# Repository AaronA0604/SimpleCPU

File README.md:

# SimpleCPU
This is a simple CPU that can follow a list of 16 instructions and perform addition, subtraction, and simple logic operations on 2-bit numbers. I made this to learn how to use gates, and it is a good project for people who have experience with hardware but not with gates to try.

It works in several steps. First, the user flips switches in a matrix to manually code the instructions. Then, the user presses run, and those switches tell the ROM, another matrix, what the instructions are. Then, the user powers on the CPU with a switch and resets the counter. Then, the clock starts pulsing 1s and 0s to the counter. The counter then increments by one every clock tick, or jumps a specific amount in certain cases. Next is a decoder that, given the number instructions from the counter, selects a row in the ROM, each of which hold an instruction. The row is inputted into the ALU, which performs the selected operations. Sometimes the instruction will want to use the value from the previous operation, so the accumulator stores the values from the previous operation. Then there is a selector that decides if the ALU gets a new value or the previous output value. The ALU outputs flags, such as negative and zero, which essentially describe the output. The next section then decides whether the program should just go to the next instruction or jump to a different instruction based on those flags. It tells this to the program counter, and the program counter moves to the next part. Then it all repeats.

## Clock

This clock is made of 3 not gates, which invert the value put into them. So, if the input is 1, the output is 0. Because there are an odd number, their output value alternates between 0 and 1 every pass. The 1 is essentially a clock tick. The switch gives power the clock; without it, it can't run. Finally, the and gate is there to only output a value every tick, since it only outputs 1 when the clock value is 1.

## Program Counter (PC)
The job of the PC is to track what step we are on. It moves to the next step or jumps (I'll explain this later) every clock tick.

The first part of the PC is a multiplexer (mux) that takes the number of step we were just on, and a number from the read-only memory that is a step to jump to. It then decides whether it should increment the step we're on by 1 or jump based on an input from the branch logic part of the CPU.

The second part of the PC is an adder. It takes the output from the mux (either 1 for "go to the next step" or another number for a jump) and adds that number to the number of the previous step. It works by using XOR gates, AND gates, and OR gates.

That last part is a register (flip flops that store the value). This keeps track of what number step it is on (a 4 bit number) using 4 slave-master latches (1 for each bit). It also feeds this value back into the adder part of the PC as the value that the increment or jump is added to.

## Read-Only Memory (ROM)
The point of the ROM is to store the instructions to run, and then using the number step from the PC, access the number instruction and send it to the rest of the CPU to run.

The first part of it is a decoder that gets the output from the PC. If that output is 0110 (6), for example, then the decoder makes all of its outputs high except for the 6th output. This means that the CPU is going to run the 6th instruction stored in the ROM.

The ROM stores all of its instructions in this 16x15 matrix. Every row is an instruction, and each column is a different part of that instruction needed to make a full instruction. The matrix is made up of latching switches. They have two coils so that you can turn them on and off electronically (this will make sense when I talk about the assembler), and then they hold their value even while the CPU is off.

This is one latch in the matrix. It is the first one in its row. The row is connected to the NOT gate seen on the left, since as I said earlier the decoder turns all rows high except the one that is chosen, which it turns low. This not gate makes the chosen row high and the others low, which is needed for the CPU to work. It connects to pin 10 on the latch, which is the input pin. The +R and +S coils in this latch are connected to diodes so that their current doesn't leak. The diodes are connected to a row in the assembler (which I'll explain later) so that the latch's value can be changed. Pin 9, the output pin, is connected to a diode so that current doesn't leak to other lines. Then the diode is connected to a wire that runs all the way down the column. Every latch in the same column has a value for the same type. For example, the type could be the 2nd bit of the input value A, or the address that the PC will jump to. At the bottom of every column is a 10k resistor connected to GND.

## Arithmetic Logic Unit (ALU)
The ALU is the heart of the CPU. It does all the computations that are needed for the program. The values for the computation are stored in the ROM, as well as the operation to do to those values. It can only take in 2 values that are each 2 bits.

This part of the ALU is the adder and subtracter. It takes in the 2 2-bit values, denoted as A0, A1, B0, and B1 in this image, and adds or subtracts them based on another input. It works by using XOR gates, AND gates, and OR gates. The AND gate at the top of the image decides whether this adder/subtractor should add or subtract. The AND gate takes two inputs, S0 and S1 (I'll explain where they come from later), and outputs a 1 or 0 to say add or subtract. This output is used as the input for some of the XOR gates. This section of the ALU can both add and subtract, since for subtracting, it inverts the second number, adds it to the first, and adds 1.

This part of the ALU does 4 operations: it can see if values are both 1, see if values are different, see if at least one of the values is 1, or see if none of the values are 1. It uses AND gates, XOR gates, OR gates, and NOT gates respectively to do these different operations.

Since there are many operations that the ALU can do, these two muxes decide which operation to use. The ALU does all of the operations I talked about above the input numbers, but these muxs only let the outputs from one of the operations through. There are 2 muxs, since the inputs are 2 bit numbers and each mux can only deal with one bit. They take in all the outputs from the different operations and also S0, S1, and S2 from the ROM. The S's tell the muxs which value to let through. If those three input values are 010 (2), the muxs let the second value through. I6 on both of them is not being used, so it is tied to GND. They output F0 and F1, which go to the flags, LEDs, and accumulator.

## Flags
Often, the CPU doesn't care what the output number is; it only cares about its characteristics (negative, zero, etc.) These flags describe those characteristics. There are 3 flags: negative, zero, and overflow. Negative sees if the output is negative, zero sees if the output is zero, and overflow sees if the output was more than 2 bits (this could happen if 11 and 11 were added, for example, as that would result in 110).

These gates determine those flags about the output. Note that there are only two gates, for overflow and zero, since the negative flag is simply the output COUT from the adder. The gate for the zero flag is an NAND gate that sees if both F0 and F1 are zero. If they are, it outputs 1, saying that the output from the ALU was 0. The overflow XOR gate takes the COUT output from the adder and the output of the first OR gate in the adder and sees if they are different. If they are, it outputs 1, which means the output from the ALU was more than 2 bits.

## LEDs

These LEDs are a visual output that show both the flag values and the number. From top to bottom, they represent these values: zero flag, negative flag, overflow flag, first digit of output, second digit of output, and third digit of output or a negative sign if the value is being read as signed.

## Accumulator

The accumulator stores the outputs from the ALU in 2 master-slave latches (one for each of the 2 output bits). It takes the output value from the ALU and clock (CLK) as its inputs so it stores the output value and doesn't change it while the clock is in the middle of a tick, since that would mess up its value.

## A Select
Sometimes, we want to do an operation to 2 new values, but sometimes we want to do an operation to an old value, like in a for loop.

Because of this, we have a mux that decides if we want to use a new value for A0 and A1 or the old one. It takes the old value from the accumulator and a new value from the ROM. It also takes a value from the ROM called A_OPCODE, which determines if the output of the mux is the old or new value. Based on that, it outputs 2 bits that are sent to the ALU as the A0 and A1 values.

## Branch Logic
Sometimes, we want to skip to a different instruction based on the output of the last operation.

To decide this, we use a mux and an XOR gate. The mux takes in the flag values and ties all the other unused inputs to GND. It also takes in two bits from the ROM called FLAG0 and FLAG1. These 2 values tell the mux what flag to look at. If those values make the number 01 (1), the mux looks at the first flag. It outputs the value of that flag to the XOR. The XOR then takes another input from the ROM called FLAG_VALUE. FLAG_VALUE says if the program should jump to a different step if the flag value is 0 or 1. Then it outputs JMP to the PC mux, which I mentioned before.

## Set Clock
This is the first piece of the part of the CPU that changes the instructions in the ROM.

The first part of this is the 5-5-5 timer at the top. It and everything attached to it are the actual clock. It's a more complicated version of the clock from before. It outputs SLOW_CLK and its opposite, SLOW_CLK_N.

The AND gate under it takes output from that clock, SLOW_CLK, and also RUN_S, which I'll explain later. If both those values are true, meaning if the clock is pulsing and also RUN_S is on, then it outputs a PULSE.

The NOT gate under that inverts PULSE to PULSE_N.

Under that is a master-slave latch to store two values. It takes the input from a switch, which when it is turned on it means that this reset circuit should run. It also takes SLOW_CLK_N as its second input, and then stores the value of RUN_S and its opposite, RUN_S_N.

The last section is an AND gate that takes RUN_S_N and /RESET (which it gets from the image above) and outputs /RESET_CPU if both those values are on, meaning the set switch is on and the reset button is pressed (which is needed because otherwise the ROM will be messed up).

## Set Counter

This is the counter for the set clock that keeps track of what step it is on. It increases by one every clock pulse. Bar MR is connected to RUN_S so that it only counts if that switch is on. CP is connected to SLOW_CLK_N so that it increases every clock pulse. TC is connected to CEP with an inverter so that it can't count past 16.

This is a decoder, just like the one that connects to the ROM. It takes the value from the counter and makes that output low and every other output high, selecting that row.

## Assembler

This is the final piece in this section, and once you understand it you will understand how this section works. Remember, the point of this section is to write instructions to the ROM. This piece is a matrix that mirrors the ROM, with the same number of rows and columns. It is a bunch of switches that you switch to manually write the instructions. For example if you want the value of A1 in the third step to be one, you go to the third row in the A1 column and flip the switch on, so it is a one. The idea of this matrix is that you manually set all the values, and then you flip the RUN_S switch from before, and it writes all these values to the ROM.

This is one switch in the matrix. It is very simple. It is just connected to a diode so the current doesn't leak, and all you need to do is flip the switch and the value changes.

## Assembler connection to ROM
This is the most complicated part of the CPU. The idea behind it is that the set counter turns on the rows in the assembler one at a time. There is only one row that has power at a time. Then, the values from each of the columns in the assembler pass through gates (I'll explain these later) and a driver to give it enough power to change the values in the ROM. The value from the columns runs down its corresponding column in the ROM, and only changes a latch's value if its row is turned on. This way, by running through every row, every latch can be changed to match the assembler.

These are all the gates for the 15 columns in the ROM.

There are two for every column; one to make the latch value 0, and one to make it 1. The AND gate only lets a one through if the value inputted into it from the column in the assembler is a one, and the NOT gate only lets a one through the value inputted into it from the column in the assembler is a zero. Only one of these gates will output a one at the same time.

These two outputs then go to the driver, which makes their voltage much higher. If its input was a 1 and a 0, it would still output a 1 and a 0, only the 1 would be a higher voltage.

It sends its output to the two coils in the latch. The +S coil is to make the latch a 1, so that pin is only fed from the pin in the driver fed by the AND gate. The +R coil is to make the latch a 0, so that pin is only fed from the pin in the driver fed by the NOT gate.

## PCB

For the PCB, wire it however you'd like. This is a picture of how I wired mine, but you'll have to figure out what works for you.

I recommend adding this chart as the values that you need to set the S0, S1, and S2 columns to in the assembler to do these different operations.

It is also helpful to label your LEDs so you know what they are telling you. Additionally, you can label the columns in the assembler so you know what value each column is. This is what each column is for, from left to right: A0, A1, B0, B1, S0, S1, S2, A_OPCODE, FLAG0, FLAG1, FLAG_VALUE, ADDRESS0, ADDRESS1, ADDRESS2, ADDRESS3.

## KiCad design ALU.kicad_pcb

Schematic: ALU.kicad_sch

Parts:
C1: 10 µF; C_0805_2012Metric
C2: 0.1µF; C_0603_1608Metric
C3: 1µF; C_0603_1608Metric
C4: 10nF; C_0805_2012Metric
D1, D2, D3, D4, D5, D6, D7, D8, D9, D10, D11, D12, D13, D14, D15, D16, D17, D18, D19, D20, D21, D22, D23, D24, D25, D26, D27, D28, D29, D30, D31, D32, D33, D34, D35, D36, D37, D38, D39, D40, D41, D42, D43, D44, D45, D46, D47, D48, D49, D50, D51, D52, D53, D54, D55, D56, D57, D58, D59, D60, D61, D62, D63, D64, D65, D66, D67, D68, D69, D70, D71, D72, D73, D74, D75, D76, D77, D78, D79, D80, D81, D82, D83, D84, D85, D86, D87, D88, D89, D90, D91, D92, D93, D94, D95, D96, D103, D104, D105, D106, D107, D108, D109, D110, D111, D112, D113, D114, D115, D116, D117, D118, D119, D120, D121, D122, D123, D124, D125, D126, D127, D128, D129, D130, D131, D132, D133, D134, D135, D136, D137, D138, D139, D140, D141, D142, D143, D144, D145, D146, D147, D148, D149, D150, D151, D152, D153, D154, D155, D156, D157, D158, D159, D160, D161, D162, D163, D164, D165, D166, D167, D168, D169, D170, D171, D172, D173, D174, D175, D176, D177, D178, D179, D180, D181, D182, D183, D184, D185, D186, D187, D188, D189, D190, D191, D192, D193, D194, D195, D196, D197, D198, D199, D200, D201, D202, D203, D204, D205, D206, D207, D208, D209, D210, D211, D212, D213, D214, D215, D216, D217, D218, D219, D220, D221, D222, D223, D224, D225, D226, D227, D228, D229, D230, D231, D232, D233, D234, D235, D236, D237, D238, D239, D240, D241, D242, D243, D244, D245, D246, D247, D248, D249, D250, D251, D252, D253, D254, D255, D256, D257, D258, D259, D260, D261, D262, D263, D264, D265, D266, D267, D268, D269, D270, D271, D272, D273, D274, D275, D276, D277, D278, D279, D280, D281, D282, D283, D284, D285, D286, D287, D288, D289, D290, D291, D292, D293, D294, D295, D296, D297, D298, D299, D300, D301, D302, D303, D304, D305, D306, D307, D308, D309, D310, D311, D312, D313, D314, D315, D316, D317, D318, D319, D320, D321, D322, D323, D324, D325, D326, D327, D328, D329, D330, D331, D332, D333, D334, D335, D336, D337, D338, D339, D340, D341, D342, D343, D344, D345, D346, D347, D348, D349, D350, D351, D352, D353, D354, D355, D356, D357, D358, D359, D360, D361, D362, D363, D364, D365, D366, D367, D368, D369, D370, D371, D372, D373, D374, D375, D376, D377, D378, D379, D380, D381, D382, D383, D384, D385, D386, D387, D388, D389, D390, D391, D392, D393, D394, D395, D396, D397, D398, D399, D400, D401, D402, D403, D404, D405, D406, D407, D408, D409, D410, D411, D412, D413, D414, D415, D416, D417, D418, D419, D420, D421, D422, D423, D424, D425, D426, D427, D428, D429, D430, D431, D432, D433, D434, D435, D436, D437, D438, D439, D440, D441, D442, D443, D444, D445, D446, D447, D448, D449, D450, D451, D452, D453, D454, D455, D456, D457, D458, D459, D460, D461, D462, D463, D464, D465, D466, D467, D468, D469, D470, D471, D472, D473, D474, D475, D476, D477, D478, D479, D480, D481, D482, D483, D484, D485, D486, D487, D488, D489, D490, D491, D492, D493, D494, D495, D496, D497, D498, D499, D500, D501, D502, D503, D504, D505, D506, D507, D508, D509, D510, D511, D512, D513, D514, D515, D516, D517, D518, D519, D520, D521, D522, D523, D524, D525, D526, D527, D528, D529, D530, D531, D532, D533, D534, D535, D536, D537, D538, D539, D540, D541, D542, D543, D544, D545, D546, D547, D548, D549, D550, D551, D552, D553, D554, D555, D556, D557, D558, D559, D560, D561, D562, D563, D564, D565, D566, D567, D568, D569, D570, D571, D572, D573, D574, D575, D576, D577, D578, D579, D580, D581, D582, D583, D584, D585, D586, D587, D588, D589, D590, D591, D592, D593, D594, D595, D596, D597, D598, D599, D600, D601, D602, D603, D604, D605, D606, D607, D608, D609, D610, D611, D612, D613, D614, D615, D616, D617, D618, D619, D620, D621, D622, D623, D624, D625, D626, D627, D628, D629, D630, D631, D632, D633, D634, D635, D636, D637, D638, D639, D640, D641, D642, D643, D644, D645, D646, D647, D648, D649, D650, D651, D652, D653, D654, D655, D656, D657, D658, D659, D660, D661, D662, D663, D664, D665, D666, D667, D668, D669, D670, D671, D672, D673, D674, D675, D676, D677, D678, D679, D680, D681, D682, D683, D684, D685, D686, D687, D688, D689, D690, D691, D692, D693, D694, D695, D696, D697, D698, D699, D700, D701, D702, D703, D704, D705, D706, D707, D708, D709, D710, D711, D712, D713, D714, D715, D716, D717, D718, D719, D720, D721, D722, D723, D724, D725, D726, D727, D728, D729, D730, D731, D732, D733, D734, D735, D736, D737, D738, D739, D740, D741, D742, D743, D744, D745, D746, D747, D748, D749, D750, D751, D752, D753, D754, D755, D756, D757, D758, D759, D760, D761, D762, D763, D764, D765, D766, D767, D768, D769, D770, D771, D772, D773, D774, D775, D776, D777, D778, D779, D780, D781, D782, D783, D784, D785, D786, D787, D788, D789, D790, D791, D792, D793, D794, D795, D796, D797, D798, D799, D800, D801, D802, D803, D804, D805, D806, D807, D808, D809, D810, D811, D812, D813, D814, D815, D816, D817, D818, D819, D820, D821, D822, D823, D824, D825, D826, D827, D828, D829, D830, D831, D832, D833, D834, D835, D836, D837, D838, D839, D840, D841, D842, D843, D844, D845, D846, D847, D848, D849, D850, D851, D852, D853, D854, D855, D856, D857, D858, D859, D860, D861, D862, D863, D864, D865, D866, D867, D868, D869, D870, D871, D872, D873, D874, D875, D876, D877, D878, D879, D880, D881, D882, D883, D884, D885, D886, D887, D888, D889, D890, D891, D892, D893, D894, D895, D896, D897, D898, D899, D900, D901, D902, D903, D904, D905, D906, D907, D908, D909, D910, D911, D912, D913, D914, D915, D916, D917, D918, D919, D920, D921, D922, D923, D924, D925, D926, D927, D928, D929, D930, D931, D932, D933, D934, D935, D936, D937, D938, D939, D940, D941, D942, D943, D944, D945, D946, D947, D948, D949, D950, D951, D952, D953, D954, D955, D956, D957, D958, D959, D960, D961, D962, D963, D964, D965, D966: D; D_DO-35_SOD27_P7.62mm_Horizontal
D97, D98, D99, D100, D101, D102: LED; LED_D5.0mm
K1, K2, K3, K4, K5, K6, K7, K8, K9, K10, K11, K12, K13, K14, K15, K16, K17, K18, K19, K20, K21, K22, K23, K24, K25, K26, K27, K28, K29, K30, K31, K32, K33, K34, K35, K36, K37, K38, K39, K40, K41, K42, K43, K44, K45, K46, K47, K48, K49, K50, K51, K52, K53, K54, K55, K56, K57, K58, K59, K60, K61, K62, K63, K64, K65, K66, K67, K68, K69, K70, K71, K72, K73, K74, K75, K76, K77, K78, K79, K80, K81, K82, K83, K84, K85, K86, K87, K88, K89, K90, K91, K92, K93, K94, K95, K96, K97, K98, K99, K100, K101, K102, K103, K104, K105, K106, K107, K108, K109, K110, K111, K112, K113, K114, K115, K116, K117, K118, K119, K120, K121, K122, K123, K124, K125, K126, K127, K128, K129, K130, K131, K132, K133, K134, K135, K136, K137, K138, K139, K140, K141, K142, K143, K144, K145, K146, K147, K148, K149, K150, K151, K152, K153, K154, K155, K156, K157, K158, K159, K160, K161, K162, K163, K164, K165, K166, K167, K168, K169, K170, K171, K172, K173, K174, K175, K176, K177, K178, K179, K180, K181, K182, K183, K184, K185, K186, K187, K188, K189, K190, K191, K192, K193, K194, K195, K196, K197, K198, K199, K200, K201, K202, K203, K204, K205, K206, K207, K208, K209, K210, K211, K212, K213, K214, K215, K216, K217, K218, K219, K220, K221, K222, K223, K224, K225, K226, K227, K228, K229, K230, K231, K232, K233, K234, K235, K236, K237, K238, K239, K240: EC2-5TNU; Relay_DPDT_Kemet_EC2_NU_DoubleCoil
Q1, Q2, Q3, Q4, Q5, Q6, Q7, Q8, Q9, Q10, Q11, Q12, Q13, Q14, Q15, Q16: BC327; TO-92_Inline
R1, R2, R9, R10, R11, R12, R13, R14, R15, R16, R17, R18, R19, R20, R21, R22, R23, R41, R42, R43, R44, R45, R46, R47, R48, R49, R50, R51, R52, R53, R54, R55: 10k; R_Axial_DIN0207_L6.3mm_D2.5mm_P10.16mm_Horizontal
R3, R4, R5, R6, R7, R8: 330 Ω; R_Axial_DIN0207_L6.3mm_D2.5mm_P10.16mm_Horizontal
R24, R25, R26, R27, R28, R29, R30, R31, R32, R33, R34, R35, R36, R37, R38, R39, R40: 1k; R_Axial_DIN0207_L6.3mm_D2.5mm_P10.16mm_Horizontal
RV1: 100k; Pololu_Breakout-16_15.2x20.3mm
SW1: SW_Push; SW_PUSH_6mm
SW2, SW3, SW4, SW5, SW6, SW7, SW8, SW9, SW10, SW11, SW12, SW13, SW14, SW15, SW16, SW17, SW18, SW19, SW20, SW21, SW22, SW23, SW24, SW25, SW26, SW27, SW28, SW29, SW30, SW31, SW32, SW33, SW34, SW35, SW36, SW37, SW38, SW39, SW40, SW41, SW42, SW43, SW44, SW45, SW46, SW47, SW48, SW49, SW50, SW51, SW52, SW53, SW54, SW55, SW56, SW57, SW58, SW59, SW60, SW61, SW62, SW63, SW64, SW65, SW66, SW67, SW68, SW69, SW70, SW71, SW72, SW73, SW74, SW75, SW76, SW77, SW78, SW79, SW80, SW81, SW82, SW83, SW84, SW85, SW86, SW87, SW88, SW89, SW90, SW91, SW92, SW93, SW94, SW95, SW96, SW97, SW98, SW99, SW100, SW101, SW102, SW103, SW104, SW105, SW106, SW107, SW108, SW109, SW110, SW111, SW112, SW113, SW114, SW115, SW116, SW117, SW118, SW119, SW120, SW121, SW122, SW123, SW124, SW125, SW126, SW127, SW128, SW129, SW130, SW131, SW132, SW133, SW134, SW135, SW136, SW137, SW138, SW139, SW140, SW141, SW142, SW143, SW144, SW145, SW146, SW147, SW148, SW149, SW150, SW151, SW152, SW153, SW154, SW155, SW156, SW157, SW158, SW159, SW160, SW161, SW162, SW163, SW164, SW165, SW166, SW167, SW168, SW169, SW170, SW171, SW172, SW173, SW174, SW175, SW176, SW177, SW178, SW179, SW180, SW181, SW182, SW183, SW184, SW185, SW186, SW187, SW188, SW189, SW190, SW191, SW192, SW193, SW194, SW195, SW196, SW197, SW198, SW199, SW200, SW201, SW202, SW203, SW204, SW205, SW206, SW207, SW208, SW209, SW210, SW211, SW212, SW213, SW214, SW215, SW216, SW217, SW218, SW219, SW220, SW221, SW222, SW223, SW224, SW225, SW226, SW227, SW228, SW229, SW230, SW231, SW232, SW233, SW234, SW235, SW236, SW237, SW238, SW239, SW240, SW241, SW242, SW243: SW_SPDT; Nidec_Copal_CAS-120A
U1, U5, U10, U20, U21: 74HC86; DIP-14_W7.62mm
U2, U4, U19, U22, U34, U36, U38, U40, U44, U47, U50: 7408; DIP-14_W7.62mm
U3, U6, U23: 7432; DIP-14_W7.62mm
U7, U16, U27, U28, U29, U45: 74HC04; DIP-14_W7.62mm
U8, U9: 74LS151; DIP-16_W7.62mm
U11, U35, U37, U39, U41: 74HCT02; DIP-14_W7.62mm
U12, U24, U25, U46: 74HC74; DIP-14_W7.62mm
U13: 74LS157; DIP-16_W7.62mm
U14: 74LS153; DIP-16_W7.62mm
U15: 4077; DIP-14_W7.62mm
U17, U43: 74HC14; DIP-14_W7.62mm
U18: 74LS157; DIP-14_W7.62mm
U26, U49: 74LS154; DIP-24_W15.24mm
U30, U31, U32, U33: ULN2803A; DIP-18_W7.62mm
U42: ICM7555xB; SOIC-8_3.9x4.9mm_P1.27mm
U48: 74LS161; DIP-16_W7.62mm

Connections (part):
+5V: C2.1, Q1.1 (C), Q2.1 (C), Q3.1 (C), Q4.1 (C), Q5.1 (C), Q6.1 (C), Q7.1 (C), Q8.1 (C), Q9.1 (C), Q10.1 (C), Q11.1 (C), Q12.1 (C), Q13.1 (C), Q14.1 (C), Q15.1 (C), Q16.1 (C), R1.2, R24.1, R41.1, R42.1, R43.1, R44.1, R45.1, R46.1, R47.1, R48.1, R49.1, R50.1, R51.1, R52.1, R53.1, R54.1, R55.1, SW2.1 (A), SW3.3 (C), U1.14 (VCC), U2.14 (VCC), U3.14 (VCC), U4.14 (VCC), U5.14 (VCC), U6.14 (VCC), U8.16 (VCC), U9.16 (VCC), U10.14 (VCC), U11.14 (VCC), U12.1 (~R), U12.4 (~S), U12.10 (~S), U12.13 (~R), U12.14 (VCC), U13.16 (VCC), U14.16 (VCC), U15.14 (VDD), U16.14 (VCC), U17.14 (VCC), U18.16 (VCC), U19.14 (VCC), U20.14 (VCC), U21.14 (VCC), U22.14 (VCC), U23.14 (VCC), U24.4 (~S), U24.10 (~S), U24.14 (VCC), U25.4 (~S), U25.10 (~S), U25.14 (VCC), U26.24 (VCC), U27.14 (VCC), U28.14 (VCC), U29.14 (VCC), U30.10 (COM), U31.10 (COM), U32.10 (COM), U33.10 (COM), U34.14 (VCC), U35.14 (VCC), U36.14 (VCC), U37.14 (VCC)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
/A0: D33.1 (K), D34.1 (K), D35.1 (K), D36.1 (K), D37.1 (K), D38.1 (K), D39.1 (K), D40.1 (K), D41.1 (K), D42.1 (K), D43.1 (K), D44.1 (K), D45.1 (K), D46.1 (K), D47.1 (K), D48.1 (K), R2.1, U13.3 (I1a)
/A0_SELECTED: U1.9, U2.1, U4.1, U5.1, U6.1, U7.1, U9.13 (I6), U13.4 (Za)
/A1: D81.1 (K), D82.1 (K), D83.1 (K), D84.1 (K), D85.1 (K), D86.1 (K), D87.1 (K), D88.1 (K), D89.1 (K), D90.1 (K), D91.1 (K), D92.1 (K), D93.1 (K), D94.1 (K), D95.1 (K), D96.1 (K), R9.1, U13.6 (I1b)
/A1_SELECTED: U1.12, U2.4, U4.4, U5.4, U6.4, U13.7 (Zb)
/ACCUMULATOR0: U12.5 (Q), U13.2 (I0a)
/ACCUMULATOR1: U12.9 (Q), U13.5 (I0b)
/ADDRESS0: D565.1 (K), D566.1 (K), D567.1 (K), D568.1 (K), D569.1 (K), D570.1 (K), D571.1 (K), D572.1 (K), D573.1 (K), D574.1 (K), D575.1 (K), D576.1 (K), D577.1 (K), D578.1 (K), D579.1 (K), D580.1 (K), R19.1, U18.3 (I1a)
/ADDRESS1: D613.1 (K), D614.1 (K), D615.1 (K), D616.1 (K), D617.1 (K), D618.1 (K), D619.1 (K), D620.1 (K), D621.1 (K), D622.1 (K), D623.1 (K), D624.1 (K), D625.1 (K), D626.1 (K), D627.1 (K), D628.1 (K), R20.1, U18.6 (I1b)
/ADDRESS2: D661.1 (K), D662.1 (K), D663.1 (K), D664.1 (K), D665.1 (K), D666.1 (K), D667.1 (K), D668.1 (K), D669.1 (K), D670.1 (K), D671.1 (K), D672.1 (K), D673.1 (K), D674.1 (K), D675.1 (K), D676.1 (K), R21.1, U18.10 (I1c)
/ADDRESS3: D709.1 (K), D710.1 (K), D711.1 (K), D712.1 (K), D713.1 (K), D714.1 (K), D715.1 (K), D716.1 (K), D717.1 (K), D718.1 (K), D719.1 (K), D720.1 (K), D721.1 (K), D722.1 (K), D723.1 (K), D724.1 (K), R22.1, U18.13 (I1d)
/AND0: U4.3, U8.4 (I0)
/AND1: U4.6, U9.4 (I0)
/A_OPCODE: D373.1 (K), D374.1 (K), D375.1 (K), D376.1 (K), D377.1 (K), D378.1 (K), D379.1 (K), D380.1 (K), D381.1 (K), D382.1 (K), D383.1 (K), D384.1 (K), D385.1 (K), D386.1 (K), D387.1 (K), D388.1 (K), R15.1, U13.1 (S)
/B0: D135.1 (K), D136.1 (K), D137.1 (K), D138.1 (K), D139.1 (K), D140.1 (K), D141.1 (K), D142.1 (K), D143.1 (K), D144.1 (K), D145.1 (K), D146.1 (K), D147.1 (K), D148.1 (K), D149.1 (K), D150.1 (K), R10.1, U1.2, U4.2, U5.2, U6.2, U7.3, U8.12 (I7)
/B1: D183.1 (K), D184.1 (K), D185.1 (K), D186.1 (K), D187.1 (K), D188.1 (K), D189.1 (K), D190.1 (K), D191.1 (K), D192.1 (K), D193.1 (K), D194.1 (K), D195.1 (K), D196.1 (K), D197.1 (K), D198.1 (K), R11.1, U1.5, U4.5, U5.5, U6.5
/C0: D725.2 (A), D726.2 (A), D727.2 (A), D728.2 (A), D729.2 (A), D730.2 (A), D731.2 (A), D732.2 (A), D733.2 (A), D734.2 (A), D735.2 (A), D736.2 (A), D737.2 (A), D738.2 (A), D739.2 (A), D740.2 (A), R41.2, U34.2, U35.3
/C1: D741.2 (A), D742.2 (A), D743.2 (A), D744.2 (A), D745.2 (A), D746.2 (A), D747.2 (A), D748.2 (A), D749.2 (A), D750.2 (A), D751.2 (A), D752.2 (A), D753.2 (A), D754.2 (A), D755.2 (A), D756.2 (A), R42.2, U34.5, U35.6
/C2: D757.2 (A), D758.2 (A), D759.2 (A), D760.2 (A), D761.2 (A), D762.2 (A), D763.2 (A), D764.2 (A), D765.2 (A), D766.2 (A), D767.2 (A), D768.2 (A), D769.2 (A), D770.2 (A), D771.2 (A), D772.2 (A), R43.2, U34.10, U35.9
/C3: D773.2 (A), D774.2 (A), D775.2 (A), D776.2 (A), D777.2 (A), D778.2 (A), D779.2 (A), D780.2 (A), D781.2 (A), D782.2 (A), D783.2 (A), D784.2 (A), D785.2 (A), D786.2 (A), D787.2 (A), D788.2 (A), R44.2, U34.13, U35.12
/C4: D789.2 (A), D790.2 (A), D791.2 (A), D792.2 (A), D793.2 (A), D794.2 (A), D795.2 (A), D796.2 (A), D797.2 (A), D798.2 (A), D799.2 (A), D800.2 (A), D801.2 (A), D802.2 (A), D803.2 (A), D804.2 (A), R45.2, U36.2, U37.3
/C5: D805.2 (A), D806.2 (A), D807.2 (A), D808.2 (A), D809.2 (A), D810.2 (A), D811.2 (A), D812.2 (A), D813.2 (A), D814.2 (A), D815.2 (A), D816.2 (A), D817.2 (A), D818.2 (A), D819.2 (A), D820.2 (A), R46.2, U36.5, U37.6
/C6: D821.2 (A), D822.2 (A), D823.2 (A), D824.2 (A), D825.2 (A), D826.2 (A), D827.2 (A), D828.2 (A), D829.2 (A), D830.2 (A), D831.2 (A), D832.2 (A), D833.2 (A), D834.2 (A), D835.2 (A), D836.2 (A), R47.2, U36.10, U37.9
/C7: D837.2 (A), D838.2 (A), D839.2 (A), D840.2 (A), D841.2 (A), D842.2 (A), D843.2 (A), D844.2 (A), D845.2 (A), D846.2 (A), D847.2 (A), D848.2 (A), D849.2 (A), D850.2 (A), D851.2 (A), D852.2 (A), R48.2, U36.13, U37.12
/C8: D853.2 (A), D854.2 (A), D855.2 (A), D856.2 (A), D857.2 (A), D858.2 (A), D859.2 (A), D860.2 (A), D861.2 (A), D862.2 (A), D863.2 (A), D864.2 (A), D865.2 (A), D866.2 (A), D867.2 (A), D868.2 (A), R49.2, U38.2, U39.3
/C9: D869.2 (A), D870.2 (A), D871.2 (A), D872.2 (A), D873.2 (A), D874.2 (A), D875.2 (A), D876.2 (A), D877.2 (A), D878.2 (A), D879.2 (A), D880.2 (A), D881.2 (A), D882.2 (A), D883.2 (A), D884.2 (A), R50.2, U38.5, U39.6
/C10: D885.2 (A), D886.2 (A), D887.2 (A), D888.2 (A), D889.2 (A), D890.2 (A), D891.2 (A), D892.2 (A), D893.2 (A), D894.2 (A), D895.2 (A), D896.2 (A), D897.2 (A), D898.2 (A), D899.2 (A), D900.2 (A), R51.2, U38.10, U39.9
/C11: D901.2 (A), D902.2 (A), D903.2 (A), D904.2 (A), D905.2 (A), D906.2 (A), D907.2 (A), D908.2 (A), D909.2 (A), D910.2 (A), D911.2 (A), D912.2 (A), D913.2 (A), D914.2 (A), D915.2 (A), D916.2 (A), R52.2, U38.13, U39.12
/C12: D917.2 (A), D918.2 (A), D919.2 (A), D920.2 (A), D921.2 (A), D922.2 (A), D923.2 (A), D924.2 (A), D925.2 (A), D926.2 (A), D927.2 (A), D928.2 (A), D929.2 (A), D930.2 (A), D931.2 (A), D932.2 (A), R53.2, U40.2, U41.3
/C13: D933.2 (A), D934.2 (A), D935.2 (A), D936.2 (A), D937.2 (A), D938.2 (A), D939.2 (A), D940.2 (A), D941.2 (A), D942.2 (A), D943.2 (A), D944.2 (A), D945.2 (A), D946.2 (A), D947.2 (A), D948.2 (A), R54.2, U40.5, U41.6
/C14: D949.2 (A), D950.2 (A), D951.2 (A), D952.2 (A), D953.2 (A), D954.2 (A), D955.2 (A), D956.2 (A), D957.2 (A), D958.2 (A), D959.2 (A), D960.2 (A), D961.2 (A), D962.2 (A), D963.2 (A), D964.2 (A), R55.2, U40.10, U41.9
/CLK: U12.3 (C), U12.11 (C), U18.2 (I0a), U19.3, U24.3 (C), U24.11 (C), U25.3 (C), U25.11 (C)
/COUT: R8.1, U3.6, U10.9
/F0: R6.1, U8.5 (Z), U11.2, U12.2 (D)
/F1: R4.1, R7.1, U9.5 (Z), U11.3, U12.12 (D), U14.5 (I1a)
/FLAG0: D421.1 (K), D422.1 (K), D423.1 (K), D424.1 (K), D425.1 (K), D426.1 (K), D427.1 (K), D428.1 (K), D429.1 (K), D430.1 (K), D431.1 (K), D432.1 (K), D433.1 (K), D434.1 (K), D435.1 (K), D436.1 (K), R16.1, U14.14 (S0)
/FLAG1: D469.1 (K), D470.1 (K), D471.1 (K), D472.1 (K), D473.1 (K), D474.1 (K), D475.1 (K), D476.1 (K), D477.1 (K), D478.1 (K), D479.1 (K), D480.1 (K), D481.1 (K), D482.1 (K), D483.1 (K), D484.1 (K), R17.1, U14.2 (S1)
/FLAG_VALUE: D517.1 (K), D518.1 (K), D519.1 (K), D520.1 (K), D521.1 (K), D522.1 (K), D523.1 (K), D524.1 (K), D525.1 (K), D526.1 (K), D527.1 (K), D528.1 (K), D529.1 (K), D530.1 (K), D531.1 (K), D532.1 (K), R18.1, U15.2
/JMP: U15.3, U18.1 (S)
/NOT0: U7.2, U8.14 (I5)
/NOT1: U7.4, U9.14 (I5)
/OR0: U6.3, U8.15 (I4)
/OR1: U6.6, U9.15 (I4)
/OVERFLOW: R5.1, U10.8, U14.4 (I2a)
/PC0: U19.4, U20.1, U24.5 (Q), U26.23 (A0)
/PC1: U19.9, U20.4, U24.9 (Q), U26.22 (A1)
/PC2: U19.12, U20.9, U25.5 (Q), U26.21 (A2)
/PC3: U20.12, U25.9 (Q), U26.20 (A3)
/PC_VALUE0: U20.3, U24.2 (D)
/PC_VALUE1: U21.3, U24.12 (D)
/PC_VALUE2: U21.6, U25.2 (D)
/PC_VALUE3: U21.8, U25.12 (D)
/PULSE: U34.1, U34.4, U34.9, U34.12, U36.1, U36.4, U36.9, U36.12, U38.1, U38.4, U38.9, U38.12, U40.1, U40.4, U40.9, U44.3, U45.1
/PULSE_N: U35.2, U35.5, U35.8, U35.11, U37.2, U37.5, U37.8, U37.11, U39.2, U39.5, U39.8, U39.11, U41.2, U41.5, U41.8, U45.2
/P_ROW0: D1.2 (A), D2.2 (A), D49.2 (A), D50.2 (A), D103.2 (A), D104.2 (A), D151.2 (A), D152.2 (A), D199.2 (A), D200.2 (A), D247.2 (A), D248.2 (A), D293.2 (A), D294.2 (A), D341.2 (A), D342.2 (A), D389.2 (A), D390.2 (A), D437.2 (A), D438.2 (A), D485.2 (A), D486.2 (A), D533.2 (A), D534.2 (A), D581.2 (A), D582.2 (A), D629.2 (A), D630.2 (A), D677.2 (A), D678.2 (A), Q1.3 (E), SW4.1 (A), SW20.1 (A), SW36.1 (A), SW52.1 (A), SW68.1 (A), SW84.1 (A), SW100.1 (A), SW116.1 (A), SW132.1 (A), SW148.1 (A), SW164.1 (A), SW180.1 (A), SW196.1 (A), SW212.1 (A), SW228.1 (A)
/P_ROW1: D3.2 (A), D4.2 (A), D51.2 (A), D52.2 (A), D105.2 (A), D106.2 (A), D153.2 (A), D154.2 (A), D201.2 (A), D202.2 (A), D249.2 (A), D250.2 (A), D295.2 (A), D296.2 (A), D343.2 (A), D344.2 (A), D391.2 (A), D392.2 (A), D439.2 (A), D440.2 (A), D487.2 (A), D488.2 (A), D535.2 (A), D536.2 (A), D583.2 (A), D584.2 (A), D631.2 (A), D632.2 (A), D679.2 (A), D680.2 (A), Q2.3 (E), SW5.1 (A), SW21.1 (A), SW37.1 (A), SW53.1 (A), SW69.1 (A), SW85.1 (A), SW101.1 (A), SW117.1 (A), SW133.1 (A), SW149.1 (A), SW165.1 (A), SW181.1 (A), SW197.1 (A), SW213.1 (A), SW229.1 (A)
/P_ROW2: D5.2 (A), D6.2 (A), D53.2 (A), D54.2 (A), D107.2 (A), D108.2 (A), D155.2 (A), D156.2 (A), D203.2 (A), D204.2 (A), D251.2 (A), D252.2 (A), D297.2 (A), D298.2 (A), D345.2 (A), D346.2 (A), D393.2 (A), D394.2 (A), D441.2 (A), D442.2 (A), D489.2 (A), D490.2 (A), D537.2 (A), D538.2 (A), D585.2 (A), D586.2 (A), D633.2 (A), D634.2 (A), D681.2 (A), D682.2 (A), Q3.3 (E), SW6.1 (A), SW22.1 (A), SW38.1 (A), SW54.1 (A), SW70.1 (A), SW86.1 (A), SW102.1 (A), SW118.1 (A), SW134.1 (A), SW150.1 (A), SW166.1 (A), SW182.1 (A), SW198.1 (A), SW214.1 (A), SW230.1 (A)
/P_ROW3: D7.2 (A), D8.2 (A), D55.2 (A), D56.2 (A), D109.2 (A), D110.2 (A), D157.2 (A), D158.2 (A), D205.2 (A), D206.2 (A), D299.2 (A), D300.2 (A), D347.2 (A), D348.2 (A), D395.2 (A), D396.2 (A), D443.2 (A), D444.2 (A), D491.2 (A), D492.2 (A), D539.2 (A), D540.2 (A), D587.2 (A), D588.2 (A), D635.2 (A), D636.2 (A), D683.2 (A), D684.2 (A), D965.2 (A), D966.2 (A), Q4.3 (E), SW7.1 (A), SW23.1 (A), SW39.1 (A), SW55.1 (A), SW71.1 (A), SW87.1 (A), SW103.1 (A), SW119.1 (A), SW135.1 (A), SW151.1 (A), SW167.1 (A), SW183.1 (A), SW199.1 (A), SW215.1 (A), SW231.1 (A)
/P_ROW4: D9.2 (A), D10.2 (A), D57.2 (A), D58.2 (A), D111.2 (A), D112.2 (A), D159.2 (A), D160.2 (A), D207.2 (A), D208.2 (A), D253.2 (A), D254.2 (A), D301.2 (A), D302.2 (A), D349.2 (A), D350.2 (A), D397.2 (A), D398.2 (A), D445.2 (A), D446.2 (A), D493.2 (A), D494.2 (A), D541.2 (A), D542.2 (A), D589.2 (A), D590.2 (A), D637.2 (A), D638.2 (A), D685.2 (A), D686.2 (A), Q5.3 (E), SW8.1 (A), SW24.1 (A), SW40.1 (A), SW56.1 (A), SW72.1 (A), SW88.1 (A), SW104.1 (A), SW120.1 (A), SW136.1 (A), SW152.1 (A), SW168.1 (A), SW184.1 (A), SW200.1 (A), SW216.1 (A), SW232.1 (A)
/P_ROW5: D11.2 (A), D12.2 (A), D59.2 (A), D60.2 (A), D113.2 (A), D114.2 (A), D161.2 (A), D162.2 (A), D209.2 (A), D210.2 (A), D255.2 (A), D256.2 (A), D303.2 (A), D304.2 (A), D351.2 (A), D352.2 (A), D399.2 (A), D400.2 (A), D447.2 (A), D448.2 (A), D495.2 (A), D496.2 (A), D543.2 (A), D544.2 (A), D591.2 (A), D592.2 (A), D639.2 (A), D640.2 (A), D687.2 (A), D688.2 (A), Q6.3 (E), SW9.1 (A), SW25.1 (A), SW41.1 (A), SW57.1 (A), SW73.1 (A), SW89.1 (A), SW105.1 (A), SW121.1 (A), SW137.1 (A), SW153.1 (A), SW169.1 (A), SW185.1 (A), SW201.1 (A), SW217.1 (A), SW233.1 (A)
/P_ROW6: D13.2 (A), D14.2 (A), D61.2 (A), D62.2 (A), D115.2 (A), D116.2 (A), D163.2 (A), D164.2 (A), D211.2 (A), D212.2 (A), D257.2 (A), D258.2 (A), D305.2 (A), D306.2 (A), D353.2 (A), D354.2 (A), D401.2 (A), D402.2 (A), D449.2 (A), D450.2 (A), D497.2 (A), D498.2 (A), D545.2 (A), D546.2 (A), D593.2 (A), D594.2 (A), D641.2 (A), D642.2 (A), D689.2 (A), D690.2 (A), Q7.3 (E), SW10.1 (A), SW26.1 (A), SW42.1 (A), SW58.1 (A), SW74.1 (A), SW90.1 (A), SW106.1 (A), SW122.1 (A), SW138.1 (A), SW154.1 (A), SW170.1 (A), SW186.1 (A), SW202.1 (A), SW218.1 (A), SW234.1 (A)
/P_ROW7: D15.2 (A), D16.2 (A), D63.2 (A), D64.2 (A), D117.2 (A), D118.2 (A), D165.2 (A), D166.2 (A), D213.2 (A), D214.2 (A), D259.2 (A), D260.2 (A), D307.2 (A), D308.2 (A), D355.2 (A), D356.2 (A), D403.2 (A), D404.2 (A), D451.2 (A), D452.2 (A), D499.2 (A), D500.2 (A), D547.2 (A), D548.2 (A), D595.2 (A), D596.2 (A), D643.2 (A), D644.2 (A), D691.2 (A), D692.2 (A), Q8.3 (E), SW11.1 (A), SW27.1 (A), SW43.1 (A), SW59.1 (A), SW75.1 (A), SW91.1 (A), SW107.1 (A), SW123.1 (A), SW139.1 (A), SW155.1 (A), SW171.1 (A), SW187.1 (A), SW203.1 (A), SW219.1 (A), SW235.1 (A)
/P_ROW8: D17.2 (A), D18.2 (A), D65.2 (A), D66.2 (A), D119.2 (A), D120.2 (A), D167.2 (A), D168.2 (A), D215.2 (A), D216.2 (A), D261.2 (A), D262.2 (A), D309.2 (A), D310.2 (A), D357.2 (A), D358.2 (A), D405.2 (A), D406.2 (A), D453.2 (A), D454.2 (A), D501.2 (A), D502.2 (A), D549.2 (A), D550.2 (A), D597.2 (A), D598.2 (A), D645.2 (A), D646.2 (A), D693.2 (A), D694.2 (A), Q9.3 (E), SW12.1 (A), SW28.1 (A), SW44.1 (A), SW60.1 (A), SW76.1 (A), SW92.1 (A), SW108.1 (A), SW124.1 (A), SW140.1 (A), SW156.1 (A), SW172.1 (A), SW188.1 (A), SW204.1 (A), SW220.1 (A), SW236.1 (A)
/P_ROW9: D19.2 (A), D20.2 (A), D67.2 (A), D68.2 (A), D121.2 (A), D122.2 (A), D169.2 (A), D170.2 (A), D217.2 (A), D218.2 (A), D263.2 (A), D264.2 (A), D311.2 (A), D312.2 (A), D359.2 (A), D360.2 (A), D407.2 (A), D408.2 (A), D455.2 (A), D456.2 (A), D503.2 (A), D504.2 (A), D551.2 (A), D552.2 (A), D599.2 (A), D600.2 (A), D647.2 (A), D648.2 (A), D695.2 (A), D696.2 (A), Q10.3 (E), SW13.1 (A), SW29.1 (A), SW45.1 (A), SW61.1 (A), SW77.1 (A), SW93.1 (A), SW109.1 (A), SW125.1 (A), SW141.1 (A), SW157.1 (A), SW173.1 (A), SW189.1 (A), SW205.1 (A), SW221.1 (A), SW237.1 (A)
/P_ROW10: D21.2 (A), D22.2 (A), D69.2 (A), D70.2 (A), D123.2 (A), D124.2 (A), D171.2 (A), D172.2 (A), D219.2 (A), D220.2 (A), D265.2 (A), D266.2 (A), D313.2 (A), D314.2 (A), D361.2 (A), D362.2 (A), D409.2 (A), D410.2 (A), D457.2 (A), D458.2 (A), D505.2 (A), D506.2 (A), D553.2 (A), D554.2 (A), D601.2 (A), D602.2 (A), D649.2 (A), D650.2 (A), D697.2 (A), D698.2 (A), Q11.3 (E), SW14.1 (A), SW30.1 (A), SW46.1 (A), SW62.1 (A), SW78.1 (A), SW94.1 (A), SW110.1 (A), SW126.1 (A), SW142.1 (A), SW158.1 (A), SW174.1 (A), SW190.1 (A), SW206.1 (A), SW222.1 (A), SW238.1 (A)
/P_ROW11: D23.2 (A), D24.2 (A), D71.2 (A), D72.2 (A), D125.2 (A), D126.2 (A), D173.2 (A), D174.2 (A), D221.2 (A), D222.2 (A), D267.2 (A), D268.2 (A), D315.2 (A), D316.2 (A), D363.2 (A), D364.2 (A), D411.2 (A), D412.2 (A), D459.2 (A), D460.2 (A), D507.2 (A), D508.2 (A), D555.2 (A), D556.2 (A), D603.2 (A), D604.2 (A), D651.2 (A), D652.2 (A), D699.2 (A), D700.2 (A), Q12.3 (E), SW15.1 (A), SW31.1 (A), SW47.1 (A), SW63.1 (A), SW79.1 (A), SW95.1 (A), SW111.1 (A), SW127.1 (A), SW143.1 (A), SW159.1 (A), SW175.1 (A), SW191.1 (A), SW207.1 (A), SW223.1 (A), SW239.1 (A)
/P_ROW12: D25.2 (A), D26.2 (A), D73.2 (A), D74.2 (A), D127.2 (A), D128.2 (A), D175.2 (A), D176.2 (A), D223.2 (A), D224.2 (A), D269.2 (A), D270.2 (A), D317.2 (A), D318.2 (A), D365.2 (A), D366.2 (A), D413.2 (A), D414.2 (A), D461.2 (A), D462.2 (A), D509.2 (A), D510.2 (A), D557.2 (A), D558.2 (A), D605.2 (A), D606.2 (A), D653.2 (A), D654.2 (A), D701.2 (A), D702.2 (A), Q13.3 (E), SW16.1 (A), SW32.1 (A), SW48.1 (A), SW64.1 (A), SW80.1 (A), SW96.1 (A), SW112.1 (A), SW128.1 (A), SW144.1 (A), SW160.1 (A), SW176.1 (A), SW192.1 (A), SW208.1 (A), SW224.1 (A), SW240.1 (A)
/P_ROW13: D27.2 (A), D28.2 (A), D75.2 (A), D76.2 (A), D129.2 (A), D130.2 (A), D177.2 (A), D178.2 (A), D225.2 (A), D226.2 (A), D271.2 (A), D272.2 (A), D319.2 (A), D320.2 (A), D367.2 (A), D368.2 (A), D415.2 (A), D416.2 (A), D463.2 (A), D464.2 (A), D511.2 (A), D512.2 (A), D559.2 (A), D560.2 (A), D607.2 (A), D608.2 (A), D655.2 (A), D656.2 (A), D703.2 (A), D704.2 (A), Q14.3 (E), SW17.1 (A), SW33.1 (A), SW49.1 (A), SW65.1 (A), SW81.1 (A), SW97.1 (A), SW113.1 (A), SW129.1 (A), SW145.1 (A), SW161.1 (A), SW177.1 (A), SW193.1 (A), SW209.1 (A), SW225.1 (A), SW241.1 (A)
/P_ROW14: D29.2 (A), D30.2 (A), D77.2 (A), D78.2 (A), D131.2 (A), D132.2 (A), D179.2 (A), D180.2 (A), D227.2 (A), D228.2 (A), D273.2 (A), D274.2 (A), D321.2 (A), D322.2 (A), D369.2 (A), D370.2 (A), D417.2 (A), D418.2 (A), D465.2 (A), D466.2 (A), D513.2 (A), D514.2 (A), D561.2 (A), D562.2 (A), D609.2 (A), D610.2 (A), D657.2 (A), D658.2 (A), D705.2 (A), D706.2 (A), Q15.3 (E), SW18.1 (A), SW34.1 (A), SW50.1 (A), SW66.1 (A), SW82.1 (A), SW98.1 (A), SW114.1 (A), SW130.1 (A), SW146.1 (A), SW162.1 (A), SW178.1 (A), SW194.1 (A), SW210.1 (A), SW226.1 (A), SW242.1 (A)
/P_ROW15: D31.2 (A), D32.2 (A), D79.2 (A), D80.2 (A), D133.2 (A), D134.2 (A), D181.2 (A), D182.2 (A), D229.2 (A), D230.2 (A), D275.2 (A), D276.2 (A), D323.2 (A), D324.2 (A), D371.2 (A), D372.2 (A), D419.2 (A), D420.2 (A), D467.2 (A), D468.2 (A), D515.2 (A), D516.2 (A), D563.2 (A), D564.2 (A), D611.2 (A), D612.2 (A), D659.2 (A), D660.2 (A), D707.2 (A), D708.2 (A), Q16.3 (E), SW19.1 (A), SW35.1 (A), SW51.1 (A), SW67.1 (A), SW83.1 (A), SW99.1 (A), SW115.1 (A), SW131.1 (A), SW147.1 (A), SW163.1 (A), SW179.1 (A), SW195.1 (A), SW211.1 (A), SW227.1 (A), SW243.1 (A)
/RUN_S: U44.2, U46.5 (Q), U48.1 (~MR)
/RUN_S_N: U46.6 (~Q), U47.2, U49.18 (E0)
/S0: D231.1 (K), D232.1 (K), D233.1 (K), D234.1 (K), D235.1 (K), D236.1 (K), D237.1 (K), D238.1 (K), D239.1 (K), D240.1 (K), D241.1 (K), D242.1 (K), D243.1 (K), D244.1 (K), D245.1 (K), D246.1 (K), R12.1, U8.11 (S0), U9.11 (S0), U50.1
/S1: D277.1 (K), D278.1 (K), D279.1 (K), D280.1 (K), D281.1 (K), D282.1 (K), D283.1 (K), D284.1 (K), D285.1 (K), D286.1 (K), D287.1 (K), D288.1 (K), D289.1 (K), D290.1 (K), D291.1 (K), D292.1 (K), R13.1, U8.10 (S1), U9.10 (S1), U50.2
/S2: D325.1 (K), D326.1 (K), D327.1 (K), D328.1 (K), D329.1 (K), D330.1 (K), D331.1 (K), D332.1 (K), D333.1 (K), D334.1 (K), D335.1 (K), D336.1 (K), D337.1 (K), D338.1 (K), D339.1 (K), D340.1 (K), R14.1, U8.9 (S2), U9.9 (S2)
/SLOW_CLK: U42.3 (OUT), U43.1, U44.1
/SLOW_CLK_N: U43.2, U46.3 (C), U48.2 (CP)
/SUB: U1.1, U1.4, U2.9, U10.1, U50.3
/SUM0: U8.1 (I3), U8.2 (I2), U10.3
/SUM1: U9.1 (I3), U9.2 (I2), U10.6
/XOR0: U5.3, U8.3 (I1)
/XOR1: U5.6, U9.3 (I1)
/ZERO: R3.1, U11.1, U14.6 (I0a)
/Za: U18.4 (Za), U19.5, U20.2
/Zb: U18.7 (Zb), U19.10, U20.5
/Zc: U18.9 (Zc), U19.13, U20.10
/Zd: U18.12 (Zd), U20.13
//RESET: U17.4, U47.1
//RESET_CPU: U24.1 (~R), U24.13 (~R), U25.1 (~R), U25.13 (~R), U47.3
GND: C1.2, C2.2, C3.2, C4.1, D97.1 (K), D98.1 (K), D99.1 (K), D100.1 (K), D101.1 (K), D102.1 (K), R2.2, R9.2, R10.2, R11.2, R12.2, R13.2, R14.2, R15.2, R16.2, R17.2, R18.2, R19.2, R20.2, R21.2, R22.2, SW1.2, SW2.3 (C), SW3.1 (A), U1.7 (GND), U2.7 (GND), U3.7 (GND), U4.7 (GND), U5.7 (GND), U6.7 (GND), U8.7 (~E), U8.8 (GND), U8.13 (I6), U9.7 (~E), U9.8 (GND), U9.12 (I7), U10.7 (GND), U11.7 (GND), U12.7 (GND), U13.8 (GND), U13.10 (I1c), U13.11 (I0c), U13.13 (I1d), U13.14 (I0d), U13.15 (E), U14.1 (Ea), U14.3 (I3a), U14.8 (GND), U14.10 (I0b), U14.11 (I1b), U14.12 (I2b), U14.13 (I3b), U14.15 (Eb), U15.7 (VSS), U16.7 (GND), U17.7 (GND), U18.5 (I0b), U18.8 (GND), U18.11 (I0c), U18.14 (I0d), U18.15 (E), U19.7 (GND), U20.7 (GND), U21.7 (GND), U22.7 (GND), U23.7 (GND), U24.7 (GND), U25.7 (GND), U26.12 (GND), U26.18 (E0), U26.19 (E1), U27.7 (GND), U28.7 (GND), U29.7 (GND), U30.9 (GND), U31.9 (GND)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
unnamed: C1.1, R1.1, SW1.1, U17.1
unnamed: D1.1 (K), K1.6
unnamed: D2.1 (K), K1.1
unnamed: D3.1 (K), K2.6
unnamed: D4.1 (K), K2.1
unnamed: D5.1 (K), K3.6
unnamed: D6.1 (K), K3.1
unnamed: D7.1 (K), K4.6
unnamed: D8.1 (K), K4.1
unnamed: D9.1 (K), K5.6
unnamed: D10.1 (K), K5.1
unnamed: D11.1 (K), K6.6
unnamed: D12.1 (K), K6.1
unnamed: D13.1 (K), K7.6
unnamed: D14.1 (K), K7.1
unnamed: D15.1 (K), K8.6
unnamed: D16.1 (K), K8.1
unnamed: D17.1 (K), K9.6
unnamed: D18.1 (K), K9.1
unnamed: D19.1 (K), K10.6
unnamed: D20.1 (K), K10.1
unnamed: D21.1 (K), K11.6
unnamed: D22.1 (K), K11.1
unnamed: D23.1 (K), K12.6
unnamed: D24.1 (K), K12.1
unnamed: D25.1 (K), K13.6
unnamed: D26.1 (K), K13.1
unnamed: D27.1 (K), K14.6
unnamed: D28.1 (K), K14.1
unnamed: D29.1 (K), K15.6
unnamed: D30.1 (K), K15.1
unnamed: D31.1 (K), K16.6
unnamed: D32.1 (K), K16.1
unnamed: D33.2 (A), K1.9
unnamed: D34.2 (A), K2.9
unnamed: D35.2 (A), K3.9
unnamed: D36.2 (A), K4.9
unnamed: D37.2 (A), K5.9
unnamed: D38.2 (A), K6.9
unnamed: D39.2 (A), K7.9
unnamed: D40.2 (A), K8.9
unnamed: D41.2 (A), K9.9
unnamed: D42.2 (A), K10.9
unnamed: D43.2 (A), K11.9
unnamed: D44.2 (A), K12.9
unnamed: D45.2 (A), K13.9
unnamed: D46.2 (A), K14.9
unnamed: D47.2 (A), K15.9
unnamed: D48.2 (A), K16.9
unnamed: D49.1 (K), K17.6
unnamed: D50.1 (K), K17.1
unnamed: D51.1 (K), K18.6
unnamed: D52.1 (K), K18.1
unnamed: D53.1 (K), K19.6
unnamed: D54.1 (K), K19.1
unnamed: D55.1 (K), K20.6
unnamed: D56.1 (K), K20.1
unnamed: D57.1 (K), K21.6
unnamed: D58.1 (K), K21.1
unnamed: D59.1 (K), K22.6
unnamed: D60.1 (K), K22.1
unnamed: D61.1 (K), K23.6
unnamed: D62.1 (K), K23.1
unnamed: D63.1 (K), K24.6
unnamed: D64.1 (K), K24.1
unnamed: D65.1 (K), K25.6
unnamed: D66.1 (K), K25.1
unnamed: D67.1 (K), K26.6
unnamed: D68.1 (K), K26.1
unnamed: D69.1 (K), K27.6
unnamed: D70.1 (K), K27.1
unnamed: D71.1 (K), K28.6
unnamed: D72.1 (K), K28.1
unnamed: D73.1 (K), K29.6
unnamed: D74.1 (K), K29.1
unnamed: D75.1 (K), K30.6
unnamed: D76.1 (K), K30.1
unnamed: D77.1 (K), K31.6
unnamed: D78.1 (K), K31.1
unnamed: D79.1 (K), K32.6
unnamed: D80.1 (K), K32.1
unnamed: D81.2 (A), K17.9
unnamed: D82.2 (A), K18.9
unnamed: D83.2 (A), K19.9
unnamed: D84.2 (A), K20.9
unnamed: D85.2 (A), K21.9
unnamed: D86.2 (A), K22.9
unnamed: D87.2 (A), K23.9
unnamed: D88.2 (A), K24.9
unnamed: D89.2 (A), K25.9
unnamed: D90.2 (A), K26.9
unnamed: D91.2 (A), K27.9
unnamed: D92.2 (A), K28.9
unnamed: D93.2 (A), K29.9
unnamed: D94.2 (A), K30.9
unnamed: D95.2 (A), K31.9
unnamed: D96.2 (A), K32.9
unnamed: D97.2 (A), R3.2
unnamed: D98.2 (A), R6.2
unnamed: D99.2 (A), R4.2
unnamed: D100.2 (A), R5.2
unnamed: D101.2 (A), R7.2
unnamed: D102.2 (A), R8.2
unnamed: D103.1 (K), K33.6
unnamed: D104.1 (K), K33.1
unnamed: D105.1 (K), K34.6
unnamed: D106.1 (K), K34.1
unnamed: D107.1 (K), K35.6
unnamed: D108.1 (K), K35.1
unnamed: D109.1 (K), K36.6
unnamed: D110.1 (K), K36.1
unnamed: D111.1 (K), K37.6
unnamed: D112.1 (K), K37.1
unnamed: D113.1 (K), K38.6
unnamed: D114.1 (K), K38.1
unnamed: D115.1 (K), K39.6
unnamed: D116.1 (K), K39.1
unnamed: D117.1 (K), K40.6
unnamed: D118.1 (K), K40.1
unnamed: D119.1 (K), K41.6
unnamed: D120.1 (K), K41.1
unnamed: D121.1 (K), K42.6
unnamed: D122.1 (K), K42.1
unnamed: D123.1 (K), K43.6
unnamed: D124.1 (K), K43.1
unnamed: D125.1 (K), K44.6
unnamed: D126.1 (K), K44.1
unnamed: D127.1 (K), K45.6
unnamed: D128.1 (K), K45.1
unnamed: D129.1 (K), K46.6
unnamed: D130.1 (K), K46.1
unnamed: D131.1 (K), K47.6
unnamed: D132.1 (K), K47.1
unnamed: D133.1 (K), K48.6
unnamed: D134.1 (K), K48.1
unnamed: D135.2 (A), K33.9
unnamed: D136.2 (A), K34.9
unnamed: D137.2 (A), K35.9
unnamed: D138.2 (A), K36.9
unnamed: D139.2 (A), K37.9
unnamed: D140.2 (A), K38.9
unnamed: D141.2 (A), K39.9
unnamed: D142.2 (A), K40.9
unnamed: D143.2 (A), K41.9
unnamed: D144.2 (A), K42.9
unnamed: D145.2 (A), K43.9
unnamed: D146.2 (A), K44.9
unnamed: D147.2 (A), K45.9
unnamed: D148.2 (A), K46.9
unnamed: D149.2 (A), K47.9
unnamed: D150.2 (A), K48.9
unnamed: D151.1 (K), K49.6
unnamed: D152.1 (K), K49.1
unnamed: D153.1 (K), K50.6
unnamed: D154.1 (K), K50.1
unnamed: D155.1 (K), K51.6
unnamed: D156.1 (K), K51.1
unnamed: D157.1 (K), K52.6
unnamed: D158.1 (K), K52.1
unnamed: D159.1 (K), K53.6
unnamed: D160.1 (K), K53.1
unnamed: D161.1 (K), K54.6
unnamed: D162.1 (K), K54.1
unnamed: D163.1 (K), K55.6
unnamed: D164.1 (K), K55.1
unnamed: D165.1 (K), K56.6
unnamed: D166.1 (K), K56.1
unnamed: D167.1 (K), K57.6
unnamed: D168.1 (K), K57.1
unnamed: D169.1 (K), K58.6
unnamed: D170.1 (K), K58.1
unnamed: D171.1 (K), K59.6
unnamed: D172.1 (K), K59.1
unnamed: D173.1 (K), K60.6
unnamed: D174.1 (K), K60.1
unnamed: D175.1 (K), K61.6
unnamed: D176.1 (K), K61.1
unnamed: D177.1 (K), K62.6
unnamed: D178.1 (K), K62.1
unnamed: D179.1 (K), K63.6
unnamed: D180.1 (K), K63.1
unnamed: D181.1 (K), K64.6
unnamed: D182.1 (K), K64.1
unnamed: D183.2 (A), K49.9
unnamed: D184.2 (A), K50.9
unnamed: D185.2 (A), K51.9
unnamed: D186.2 (A), K52.9
unnamed: D187.2 (A), K53.9
unnamed: D188.2 (A), K54.9
unnamed: D189.2 (A), K55.9
unnamed: D190.2 (A), K56.9
unnamed: D191.2 (A), K57.9
unnamed: D192.2 (A), K58.9
unnamed: D193.2 (A), K59.9
unnamed: D194.2 (A), K60.9
unnamed: D195.2 (A), K61.9
unnamed: D196.2 (A), K62.9
unnamed: D197.2 (A), K63.9
unnamed: D198.2 (A), K64.9
unnamed: D199.1 (K), K65.6
unnamed: D200.1 (K), K65.1
unnamed: D201.1 (K), K66.6
unnamed: D202.1 (K), K66.1
unnamed: D203.1 (K), K67.6
unnamed: D204.1 (K), K67.1
unnamed: D205.1 (K), K68.6
unnamed: D206.1 (K), K68.1
unnamed: D207.1 (K), K69.6
unnamed: D208.1 (K), K69.1
unnamed: D209.1 (K), K70.6
unnamed: D210.1 (K), K70.1
unnamed: D211.1 (K), K71.6
unnamed: D212.1 (K), K71.1
unnamed: D213.1 (K), K72.6
unnamed: D214.1 (K), K72.1
unnamed: D215.1 (K), K73.6
unnamed: D216.1 (K), K73.1
unnamed: D217.1 (K), K74.6
unnamed: D218.1 (K), K74.1
unnamed: D219.1 (K), K75.6
unnamed: D220.1 (K), K75.1
unnamed: D221.1 (K), K76.6
unnamed: D222.1 (K), K76.1
unnamed: D223.1 (K), K77.6
unnamed: D224.1 (K), K77.1
unnamed: D225.1 (K), K78.6
unnamed: D226.1 (K), K78.1
unnamed: D227.1 (K), K79.6
unnamed: D228.1 (K), K79.1
unnamed: D229.1 (K), K80.6
unnamed: D230.1 (K), K80.1
unnamed: D231.2 (A), K65.9
unnamed: D232.2 (A), K66.9
unnamed: D233.2 (A), K67.9
unnamed: D234.2 (A), K68.9
unnamed: D235.2 (A), K69.9
unnamed: D236.2 (A), K70.9
unnamed: D237.2 (A), K71.9
unnamed: D238.2 (A), K72.9
unnamed: D239.2 (A), K73.9
unnamed: D240.2 (A), K74.9
unnamed: D241.2 (A), K75.9
unnamed: D242.2 (A), K76.9
unnamed: D243.2 (A), K77.9
unnamed: D244.2 (A), K78.9
unnamed: D245.2 (A), K79.9
unnamed: D246.2 (A), K80.9
unnamed: D247.1 (K), K81.6
unnamed: D248.1 (K), K81.1
unnamed: D249.1 (K), K82.6
unnamed: D250.1 (K), K82.1
unnamed: D251.1 (K), K83.6
unnamed: D252.1 (K), K83.1
unnamed: D253.1 (K), K85.6
unnamed: D254.1 (K), K85.1
unnamed: D255.1 (K), K86.6
unnamed: D256.1 (K), K86.1
unnamed: D257.1 (K), K87.6
unnamed: D258.1 (K), K87.1
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
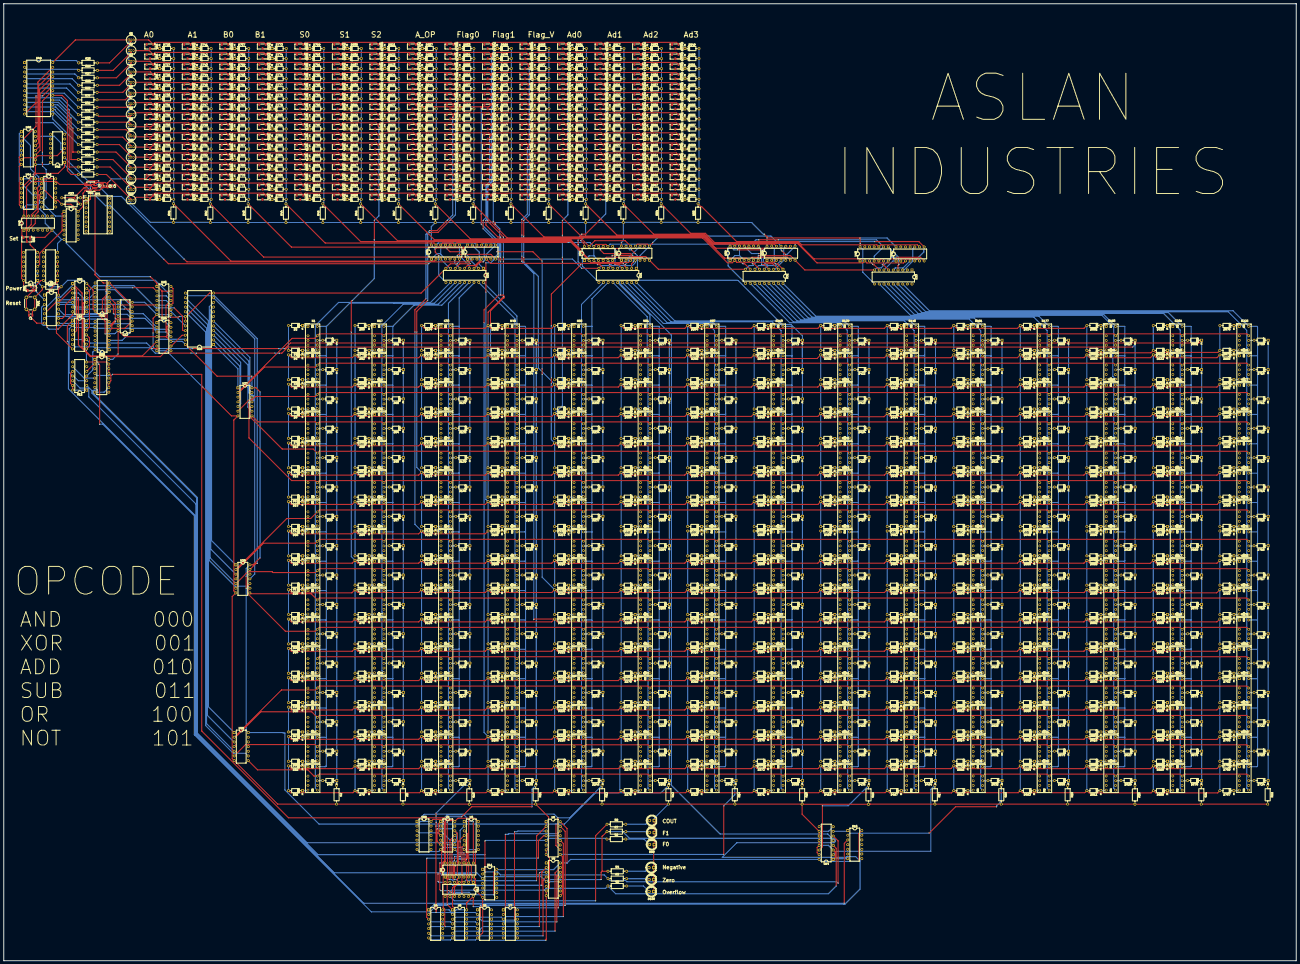
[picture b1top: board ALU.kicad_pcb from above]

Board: 2 copper layers, 701.0 x 519.0 mm, 1575 parts (0 on the bottom side), 1217 nets.
